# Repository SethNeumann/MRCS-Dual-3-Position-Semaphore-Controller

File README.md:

# REPO NAME:MRCS-Dual-3-Position-Semaphore-Controller
## License: Creative Commons Attribution-NonCommercial-ShareAlike

MRCS-Dual-3-Position-Semaphore-Controller based on Arduino Nano

Based on the PCR Arduino clinic board which was a project board for a basic Arduino class.  
- 69x100 mm
- cutouts for 2 SG90 servos facing in so they can be used for a 2 bladed semaphore or train order board
or with the servo horns facing out it should be useful as a grade crossing controller in HO or N
- Each servo has 3 analog inputs for adjustment pots, to set positions for STOP, APPPROACH and CLEAR
3 active low inputs for blade position (but the code will be at the STOP position in the abscence of 
any input, so you could get away with 2 inputs) to keep the same inputs as a search light or type "D" 
stoplight style signal, and an output for a servo

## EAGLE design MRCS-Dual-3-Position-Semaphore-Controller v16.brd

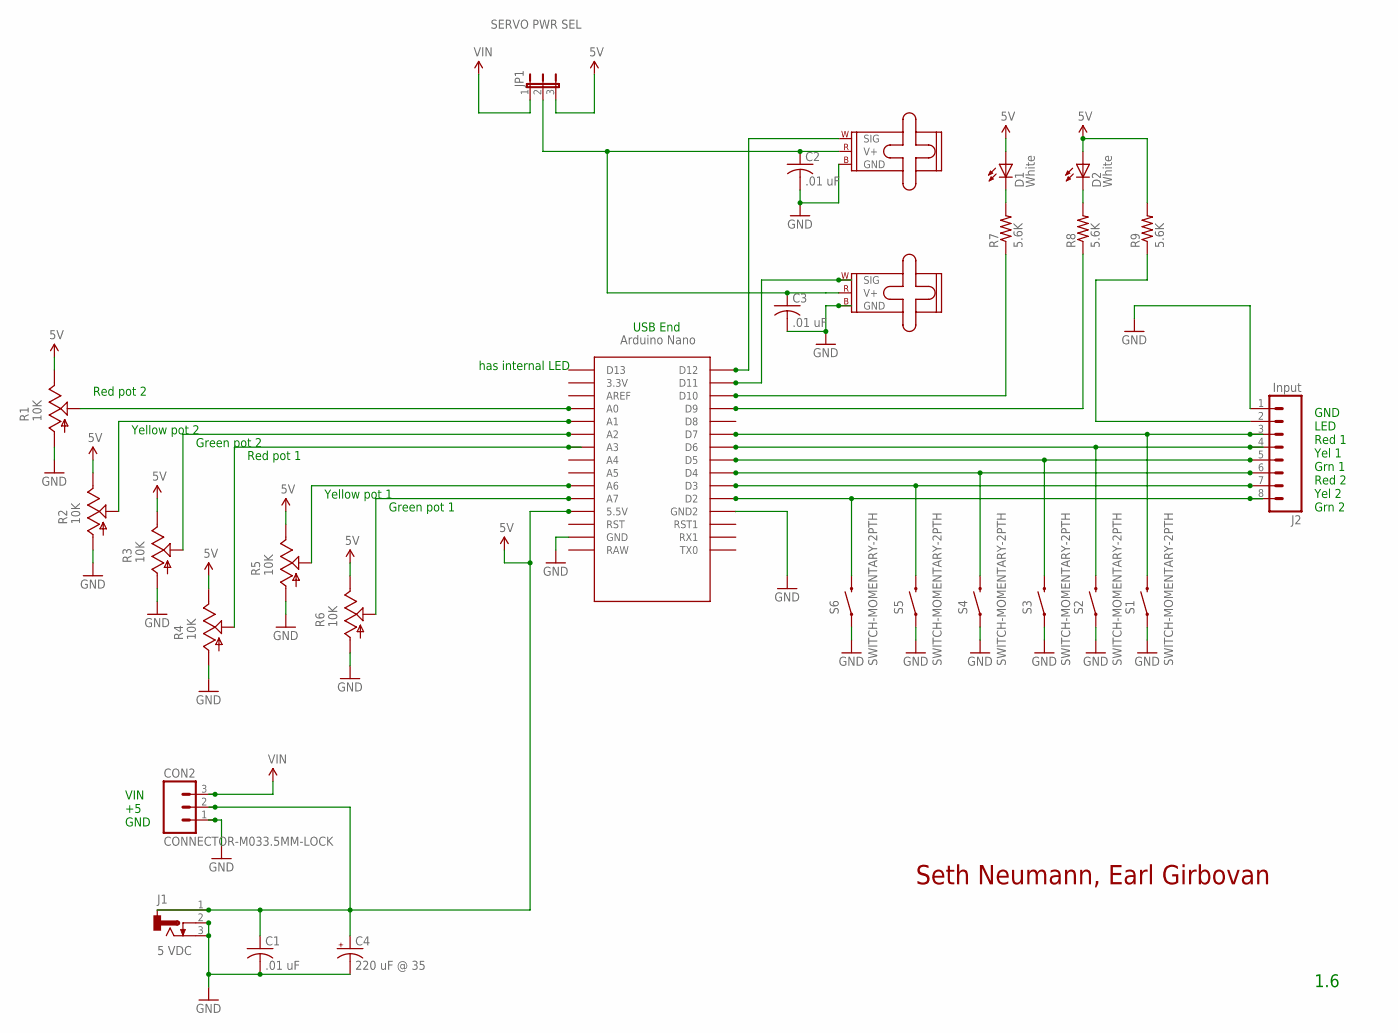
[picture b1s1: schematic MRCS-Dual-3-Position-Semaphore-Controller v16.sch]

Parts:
C1, C2, C3: .01 uF; C050-024X044
C4: 220 uF @ 35; E5-10.5
CON2: CONNECTOR-M033.5MM-LOCK; SCREWTERMINAL-3.5MM-3_LOCK.007S
D1, D2: White; LED3MM
J1: 5 VDC; DCJ0202
J2: Input; 1X08_LOCK
JP1: SERVO PWR SEL; 1X03
M1, M2: SMALL_SERVO; 1X03
NANO: NANO
R1, R2, R3, R4, R5, R6: 10K; RS3
R7, R8, R9: 5.6K; AXIAL-0.4
S1, S2, S3, S4, S5, S6: SWITCH-MOMENTARY-2PTH; TACTILE-PTH

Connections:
5V: C1.1, C4.+, CON2.2, D1.A, D2.A, J1.1, JP1.3, NANO.5V (5.5V), R1.E, R2.E, R3.E, R4.E, R5.E, R6.E, R9.P$2 (2)
A0: NANO.A0, R1.S
A1: NANO.A1, R2.S
A2: NANO.A2, R3.S
A3: NANO.A3, R4.S
A6: NANO.A6, R5.S
A7: NANO.A7, R6.S
D2: J2.8, NANO.D2, S6.3 (2)
D3: J2.7, NANO.D3, S5.3 (2)
D4: J2.6, NANO.D4, S4.3 (2)
D5: J2.5, NANO.D5, S3.3 (2)
D6: J2.4, NANO.D6, S2.3 (2)
D7: J2.3, NANO.D7, S1.3 (2)
D10: NANO.D10, R7.P$1 (1)
D11: M2.1 (SIG), NANO.D11
D12: M1.1 (SIG), NANO.D12
GND: C1.2, C2.2, C3.2, C4.-, CON2.1, J1.2, J1.3, J2.1, M1.3 (GND), M2.3 (GND), NANO.GND, NANO.GND1 (GND2), R1.A, R2.A, R3.A, R4.A, R5.A, R6.A, S1.1, S2.1, S3.1, S4.1, S5.1, S6.1
unnamed: J2.2, R9.P$1 (1)
unnamed: D1.K (C), R7.P$2 (2)
unnamed: D2.K (C), R8.P$2 (2)
unnamed: NANO.D9, R8.P$1 (1)
SERVO_SUP: C2.1, C3.1, JP1.2, M1.2 (V+), M2.2 (V+)
VIN: CON2.3, JP1.1

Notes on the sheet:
has internal LED
Red pot 2
Yellow pot 2
Green pot 2
Red pot 1
Yellow pot 1
Green pot 1
GND LED Red 1 Yel 1 Grn 1 Red 2 Yel 2 Grn 2
USB End
Seth Neumann, Earl Girbovan
1.6
VIN +5 GND

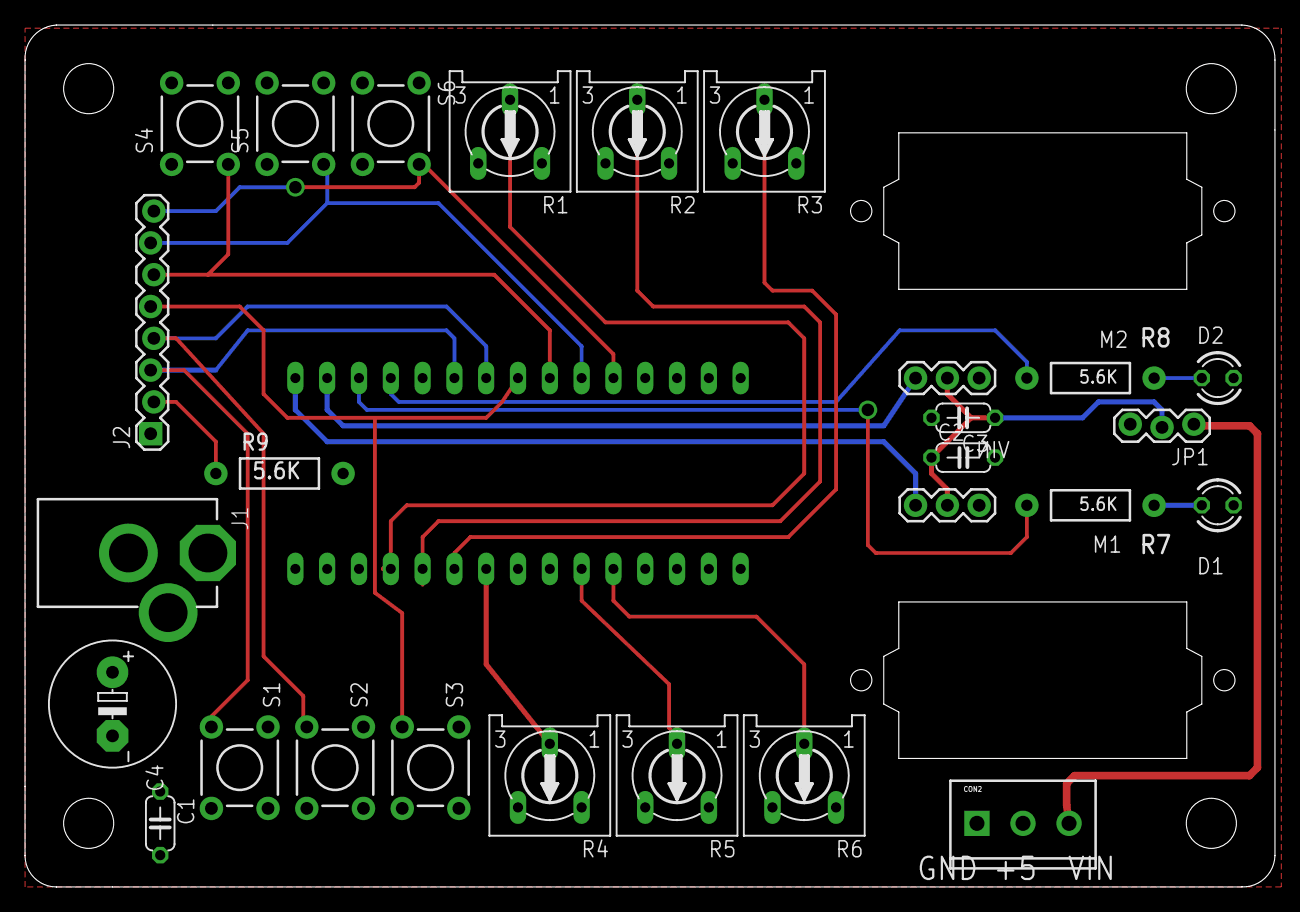
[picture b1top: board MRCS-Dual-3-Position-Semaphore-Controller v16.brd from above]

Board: 2 copper layers, 99.8 x 68.8 mm, 33 parts (0 on the bottom side), 23 nets.

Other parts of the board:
U$1: BOARD-DINRAIL-2.7IN
U$2, U$4: SERVO-9G
U$3: MRCSLOGOBTM
U$5: CA-PROP65WARNING

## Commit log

2020-12-15 intital commit
    initial commit
2020-12-15 initial commit
    initial commit
2020-12-15 Update INFO
2020-12-15 inital commit
    initial commit
2020-12-28 renumbered board
    used run cmd-renumber
2021-08-03 Version 1.o documentation package
    includes documentation, brd, sch, zip, and sketch
2022-11-14 changed +5 screw term to LED+ out for showcase
    Showcase Miniatures suggested an output for LED to illuminate roundel. Added a resistor and repurposed the old +5 screw terminal for LED power
2023-11-21 syncing up
2023-11-21 updated documentation to show resistor R9 in V1.1
2023-11-22 adding caps to work better with cheap servos
    adding caps to work better with cheap servos. One electrolytic and 3 .01 uF (103)
2023-11-26 updates based on Holbrook's crew
    added 3.5mm power terminal, added filter caps for noisy servos
2025-08-24 uploaded 200250824
    Version 1.6 sch and brd files, updated documentation

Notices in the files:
parts and their libraries:
SparkFun-Electromechanical: Licensing: CC v3.0 Share-Alike You are welcome to use this library for commercial purposes.
